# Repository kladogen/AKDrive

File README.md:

# AKDrive
<b>Sinclair QL Microdrive Emulator</b>

This an external microdrive emulator for the sinclair QL. It utilizes a raspberry pico to do the emulation and an SD card to hold the images. It has the ability to enable or disable the hardware microdrives with the addition to the QL of two small boards between the QL and the hardware microdrives that are controlled from the emulator. In this way you get to keep your hardware microdrives and use them whenever needed. 

<b>The emulator can read from MDV images, write to them, format them and also create new formated MDVs</b>.

Also, a QL Basic application is available in mdv8_ that can be used to select directly from the QL the image to load in each drive (mdv1_ to mdv7_).

<b>All mdv images are optimized by the emulator to load with maximum speed.</b>

Four buttons are available (previous, next, enter, back) to navigate the menu and an OLED screen to display the menu.
The board design is available to download and also the UDF to program the pico. In order to avoid people selling this project on ebay I will provide one license key to any one that will request it. When you use it for the first time, a file named SerNum.txt will be created in the SD card. You just send me this number and I will reply with the key that you will place in a file named lic.txt.

In folder PCB_43 you will find the KiCad files of the PCB rev4.3. In folder QL_MDV_Control you will find the KiCad files for the boards used to control the hardware microdrives.

Enjoy!

Youtube video : https://www.youtube.com/watch?v=eIUnk80rTSo (Greek)

Enclosure : https://www.thingiverse.com/thing:6572931

I specialy want to thank for their help Nikos Doukas, Petar Pandurov and Anestis Koutsoudis who designed the enclosure!

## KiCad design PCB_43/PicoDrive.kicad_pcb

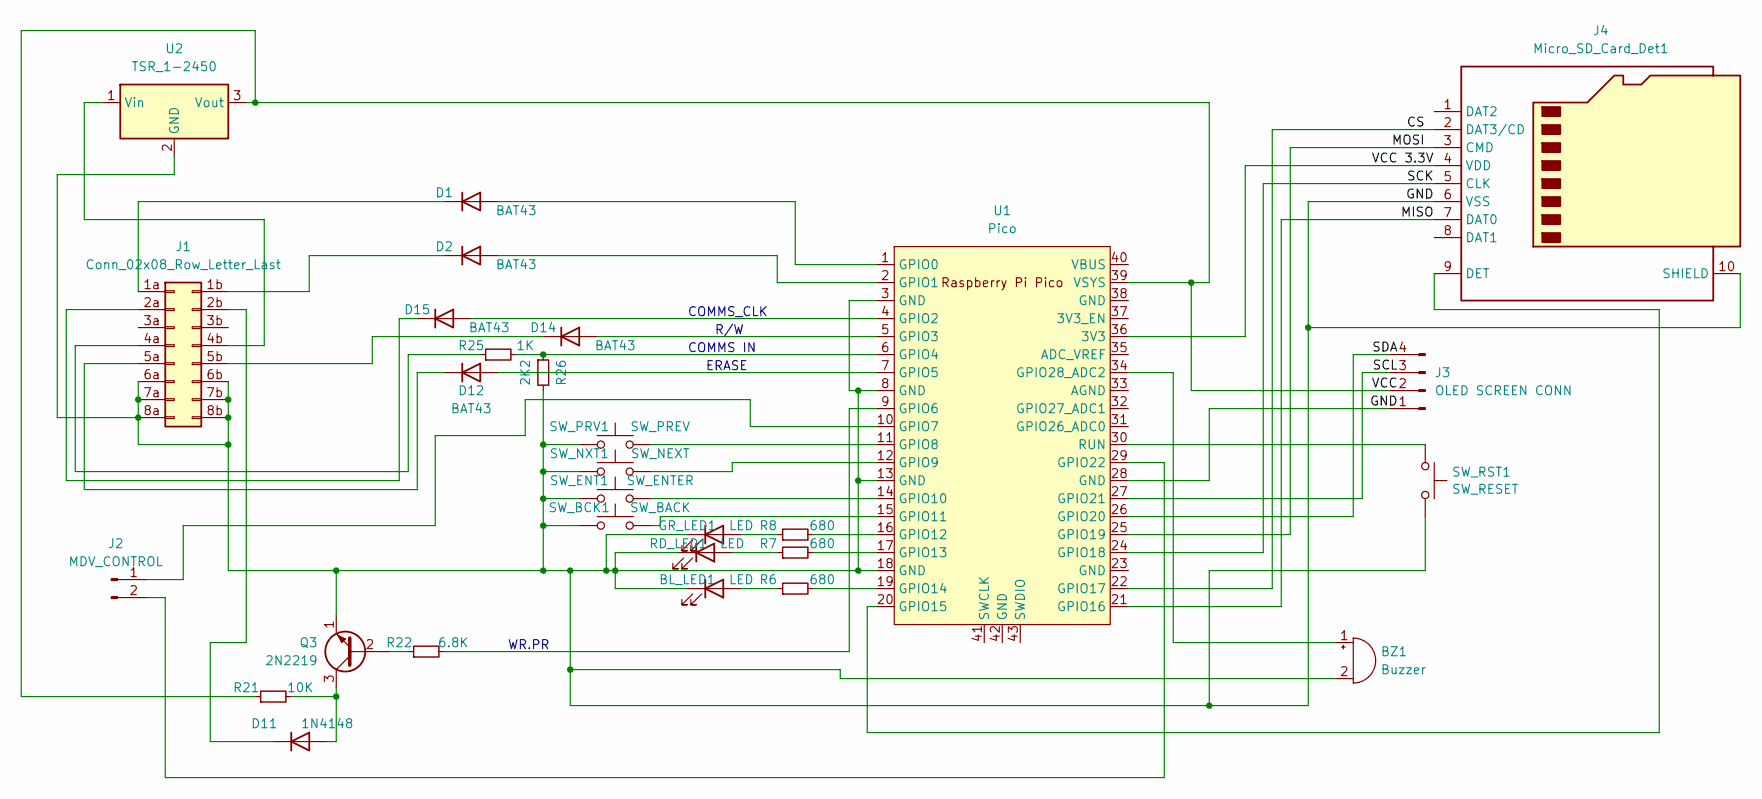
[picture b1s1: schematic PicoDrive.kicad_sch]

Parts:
BL_LED1: LED; LED_D3.0mm
BZ1: Buzzer; Buzzer_12x9.5RM7.6
D1, D2, D12, D14, D15: BAT43; D_DO-35_SOD27_P7.62mm_Horizontal
D11: 1N4148; D_DO-35_SOD27_P7.62mm_Horizontal
GR_LED1: LED; LED_D3.0mm
J1: Conn_02x08_Row_Letter_Last; PinHeader_2x08_P2.54mm_Vertical_letters
J2: MDV_CONTROL; PinHeader_1x02_P2.54mm_Vertical
J3: OLED SCREEN CONN; PinHeader_1x04_P2.54mm_Vertical
J4: Micro_SD_Card_Det1; MicroSD_Card-micro_socket_A_AliExpress
Q3: 2N2219; TO-39-3
R6, R7, R8: 680; R_Axial_DIN0204_L3.6mm_D1.6mm_P7.62mm_Horizontal
R21: 10K; R_Axial_DIN0204_L3.6mm_D1.6mm_P7.62mm_Horizontal
R22: 6.8K; R_Axial_DIN0204_L3.6mm_D1.6mm_P7.62mm_Horizontal
R25: 1K; R_Axial_DIN0204_L3.6mm_D1.6mm_P7.62mm_Horizontal
R26: 2K2; R_Axial_DIN0204_L3.6mm_D1.6mm_P7.62mm_Horizontal
RD_LED1: LED; LED_D3.0mm
SW_BCK1: SW_BACK; SW_PUSH_6mm
SW_ENT1: SW_ENTER; SW_PUSH_6mm
SW_NXT1: SW_NEXT; SW_PUSH_6mm
SW_PRV1: SW_PREV; SW_PUSH_6mm
SW_RST1: SW_RESET; SW_Tactile_SPST_Angled_PTS645Vx83-2LFS
U1: Pico; RPi_Pico_SMD_TH
U2: TSR_1-2450; Converter_DCDC_TRACO_TSR-1_THT

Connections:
/CS: J4.2 (DAT3/CD), U1.22 (GPIO17)
/GND: BL_LED1.1 (K), BZ1.2 (+), GR_LED1.1 (K), J1.6a, J1.6b, J1.7a, J1.7b, J1.8a, J1.8b, J4.6 (VSS), J4.10 (SHIELD), Q3.1 (E), R26.2, RD_LED1.1 (K), SW_BCK1.1, SW_ENT1.1, SW_NXT1.1, SW_PRV1.1, SW_RST1.2, U1.3 (GND), U1.8 (GND), U1.13 (GND), U1.18 (GND), U2.2 (GND)
/MISO: J4.7 (DAT0), U1.21 (GPIO16)
/MOSI: J4.3 (CMD), U1.25 (GPIO19)
/SCK: J4.5 (CLK), U1.24 (GPIO18)
/VCC 3.3V: J4.4 (VDD), U1.36 (3V3)
unnamed: BL_LED1.2 (A), R6.1
unnamed: BZ1.1 (-), U1.34 (GPIO28_ADC2)
unnamed: D1.2 (A), U1.1 (GPIO0)
unnamed: D1.1 (K), J1.1a
unnamed: D2.2 (A), U1.2 (GPIO1)
unnamed: D2.1 (K), J1.1b
unnamed: D11.2 (A), Q3.3 (C), R21.2
unnamed: D11.1 (K), J1.2b
unnamed: D12.2 (A), U1.7 (GPIO5)
unnamed: D12.1 (K), J1.5a
unnamed: D14.2 (A), U1.5 (GPIO3)
unnamed: D14.1 (K), J1.5b
unnamed: D15.2 (A), U1.4 (GPIO2)
unnamed: D15.1 (K), J1.2a
unnamed: GR_LED1.2 (A), R8.1
unnamed: J1.4a, R25.1
unnamed: J1.4b, U2.1 (Vin)
unnamed: J2.1, U1.10 (GPIO7)
unnamed: J2.2, U1.29 (GPIO22)
unnamed: J3.1, U1.28 (GND)
unnamed: J3.2, R21.1, U1.39 (VSYS), U2.3 (Vout)
unnamed: J3.3, U1.27 (GPIO21)
unnamed: J3.4, U1.26 (GPIO20)
unnamed: J4.9 (DET), U1.20 (GPIO15)
unnamed: Q3.2 (B), R22.1
unnamed: R7.1, RD_LED1.2 (A)
unnamed: R25.2, R26.1, U1.6 (GPIO4)
unnamed: R22.2, U1.9 (GPIO6)
unnamed: SW_PRV1.2, U1.11 (GPIO8)
unnamed: SW_NXT1.2, U1.12 (GPIO9)
unnamed: SW_ENT1.2, U1.14 (GPIO10)
unnamed: SW_BCK1.2, U1.15 (GPIO11)
unnamed: R8.2, U1.16 (GPIO12)
unnamed: R7.2, U1.17 (GPIO13)
unnamed: R6.2, U1.19 (GPIO14)
unnamed: SW_RST1.1, U1.30 (RUN)

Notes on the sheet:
R/W
ERASE
COMMS_CLK
COMMS IN
WR.PR

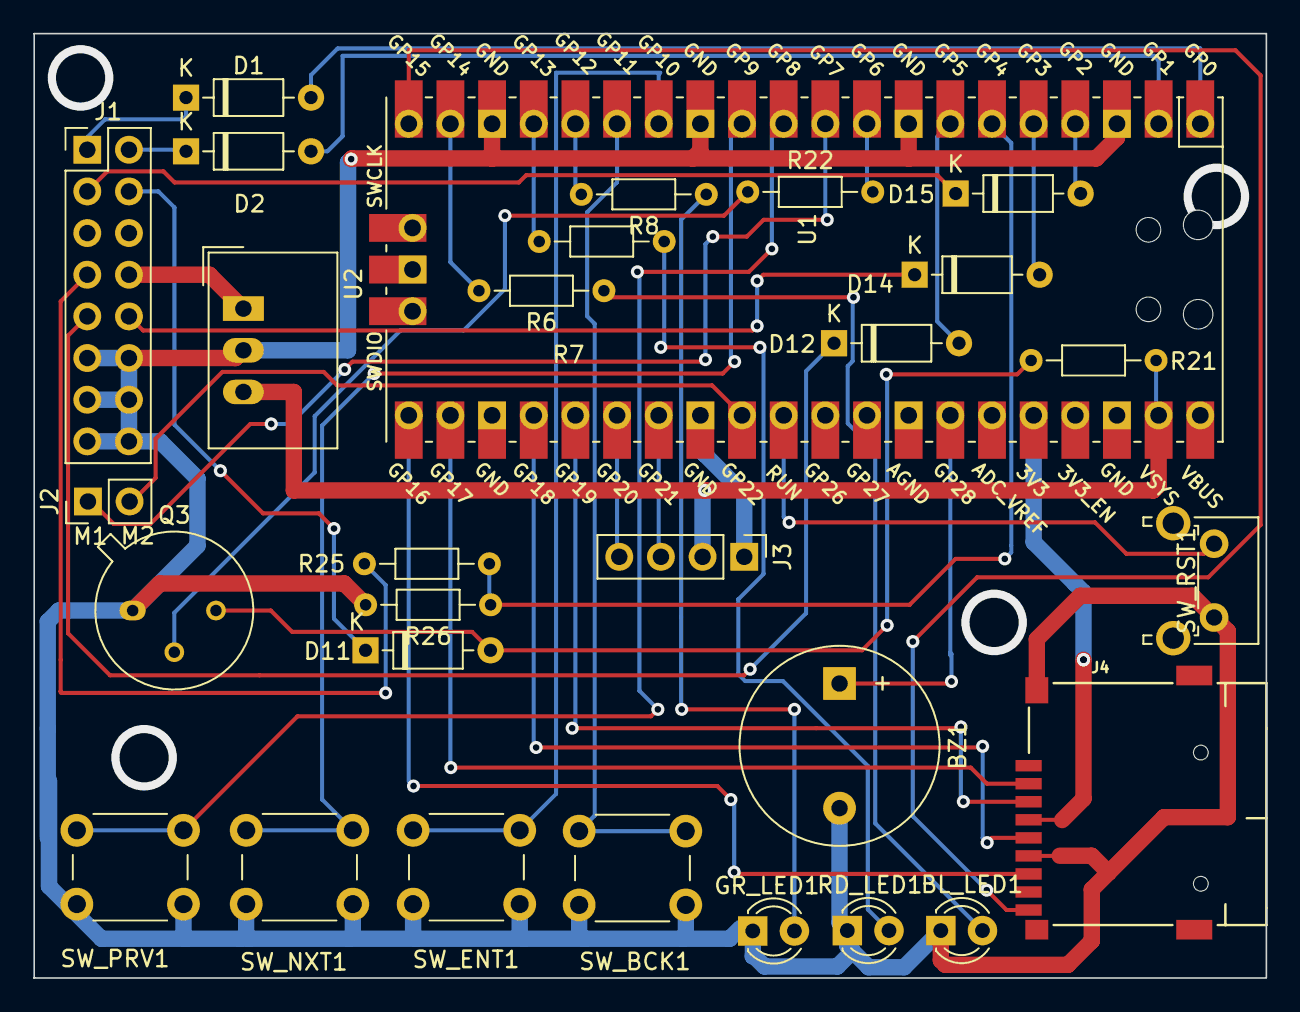
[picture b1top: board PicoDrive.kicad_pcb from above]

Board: 2 copper layers, 75.2 x 57.6 mm, 29 parts (0 on the bottom side), 42 nets.

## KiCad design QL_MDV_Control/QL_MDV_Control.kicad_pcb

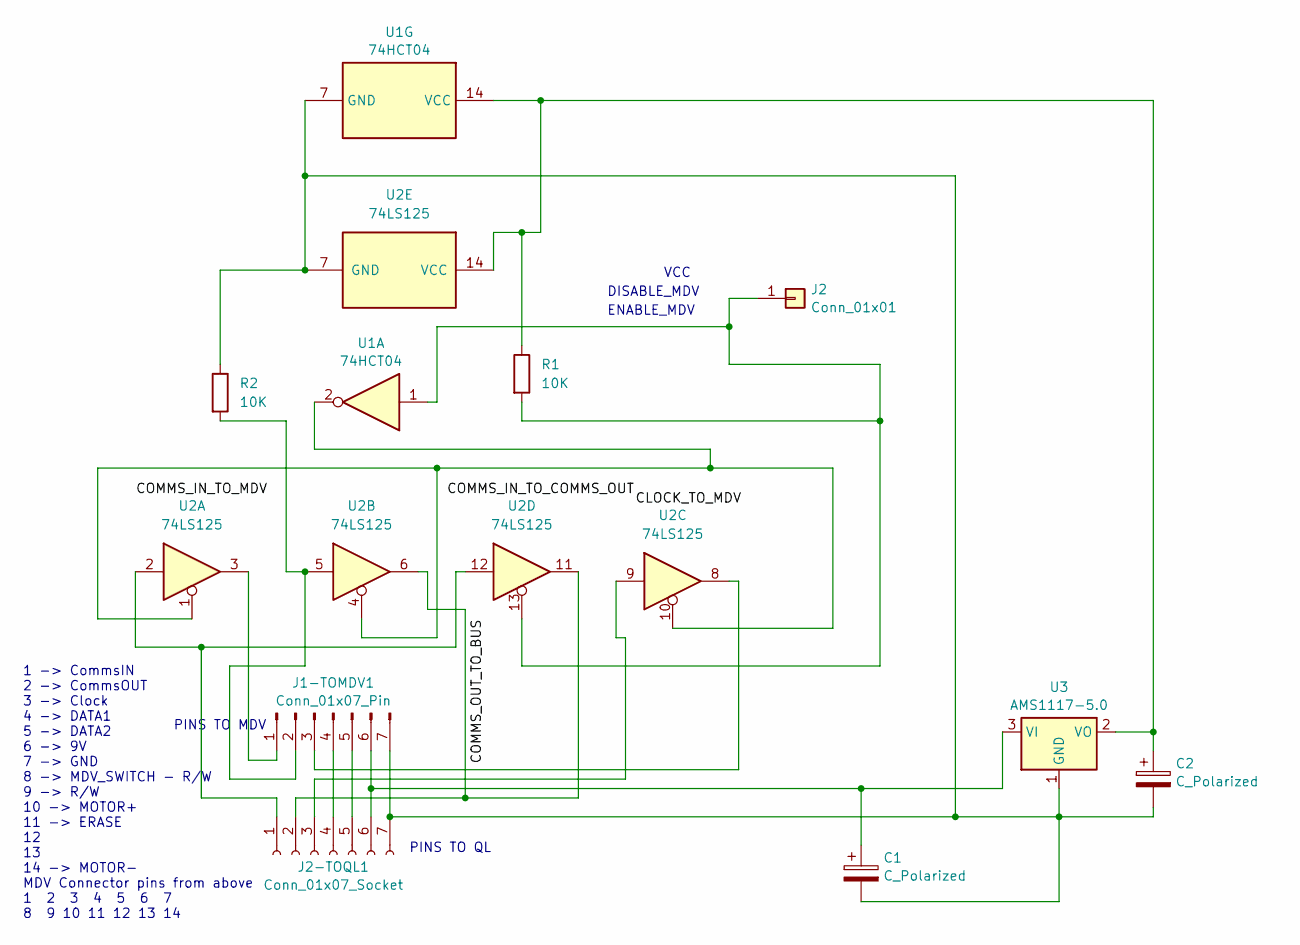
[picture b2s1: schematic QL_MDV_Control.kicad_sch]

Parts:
C1, C2: C_Polarized; CAPCP6032X280N; LCSC 2312
J1-TOMDV1: Conn_01x07_Pin; PinHeader_1x07_P2.54mm_Vertical
J2: Conn_01x01; PinHeader_1x01_P2.54mm_Vertical
J2-TOQL1: Conn_01x07_Socket; PinHeader_1x07_P2.54mm_Vertical
R1, R2: 10K; R_0805_2012Metric; LCSC CRG0805-R-103JT
U1: 74HCT04; SOIC-14_3.9x8.7mm_P1.27mm; LCSC C513511
U2: 74LS125; SOIC-14_3.9x8.7mm_P1.27mm; LCSC C133797
U3: AMS1117-5.0; SOT-89-3; LCSC C880753

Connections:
unnamed: J1-TOMDV1.1, U2.3
unnamed: J1-TOMDV1.2, R2.2, U2.5
unnamed: J1-TOMDV1.3, U2.8
unnamed: J1-TOMDV1.4, J2-TOQL1.4
unnamed: J1-TOMDV1.5, J2-TOQL1.5
unnamed: C1.1, J1-TOMDV1.6, J2-TOQL1.6, U3.3 (VI)
unnamed: C1.2, C2.2, J1-TOMDV1.7, J2-TOQL1.7, R2.1, U1.7 (GND), U2.7 (GND), U3.1 (GND)
unnamed: J2.1, R1.2, U1.1, U2.13
unnamed: J2-TOQL1.1, U2.2, U2.12
unnamed: J2-TOQL1.2, U2.6, U2.11
unnamed: J2-TOQL1.3, U2.9
unnamed: U1.2, U2.1, U2.4, U2.10
unnamed: C2.1, R1.1, U1.14 (VCC), U2.14 (VCC), U3.2 (VO)

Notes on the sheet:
VCC
ENABLE_MDV
DISABLE_MDV
PINS TO QL
PINS TO MDV
1 -> CommsIN 2 -> CommsOUT 3 -> Clock 4 -> DATA1 5 -> DATA2 6 -> 9V 7 -> GND 8 -> MDV_SWITCH - R/W 9 -> R/W 10 -> MOTOR+ 11 -> ERASE 12 13 14 -> MOTOR- MDV Connector pins from above 1 2 3 4 5 6 7 8 9 10 11 12 13 14

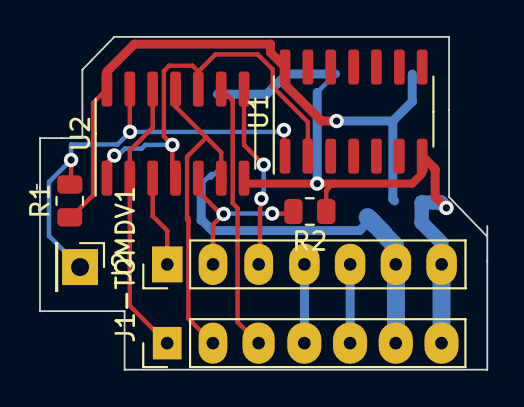
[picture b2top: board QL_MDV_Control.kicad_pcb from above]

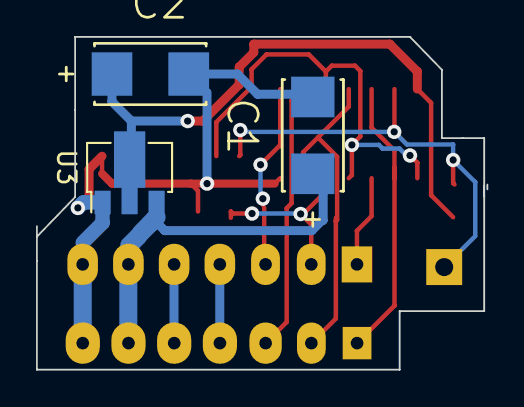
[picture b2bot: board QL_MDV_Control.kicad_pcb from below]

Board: 2 copper layers, 25.0 x 18.5 mm, 10 parts (3 on the bottom side), 13 nets.

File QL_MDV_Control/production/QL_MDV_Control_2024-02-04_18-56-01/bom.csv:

Designator,Footprint,Quantity,Value,LCSC Part #
"C1, C2",CAPCP6032X280N,2,C_Polarized,2312
J1-TOMDV1,PinHeader_1x07_P2.54mm_Vertical,1,Conn_01x07_Pin,
J2,PinHeader_1x01_P2.54mm_Vertical,1,Conn_01x01,
J2-TOQL1,PinHeader_1x07_P2.54mm_Vertical,1,Conn_01x07_Socket,
"R1, R2",0805,2,10K,CRG0805-R-103JT 
U1,SOIC-14_3.9x8.7mm_P1.27mm,1,74HCT04,C513511
U2,SOIC-14_3.9x8.7mm_P1.27mm,1,74LS125,C3754826
U3,SOT-89-3,1,AMS1117-5.0,C880753

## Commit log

2024-04-09 Create Images
2024-04-09 Changed dir name
2024-04-11 24.04.1 : Bug fixes and improvements
    Changed settings save/read in order to use a single ini type file for all settings except SN / License.
    This will enable in the future changing settings directly from the QL application.
    This version also takes care of moving parameters from old files to new Parameters.txt file.
    Fixed bug when using mdv image in mdv8_
2024-04-12 Added to PCB a connector for MDV_Control boards
2024-04-12 Info about new PCB version
